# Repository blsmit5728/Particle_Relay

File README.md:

# Particle_Relay

Inspiration Relay board: https://www.sparkfun.com/products/15093

Main Controller to be used: https://docs.particle.io/datasheets/wi-fi/photon-datasheet/

Parts Repository: https://github.com/sparkfun/SparkFun-Eagle-Libraries

Power Input Requested: USB MicroB or MiniB at 5VDC

Use Case:
- Control a Garage door opener and monitor a GPIO for Opeen/Closed Status
- D7 controls Relay state
- D0 Ouptut to sense switch 3.3VDC
- D1 Input to Read the status of the reed switch.

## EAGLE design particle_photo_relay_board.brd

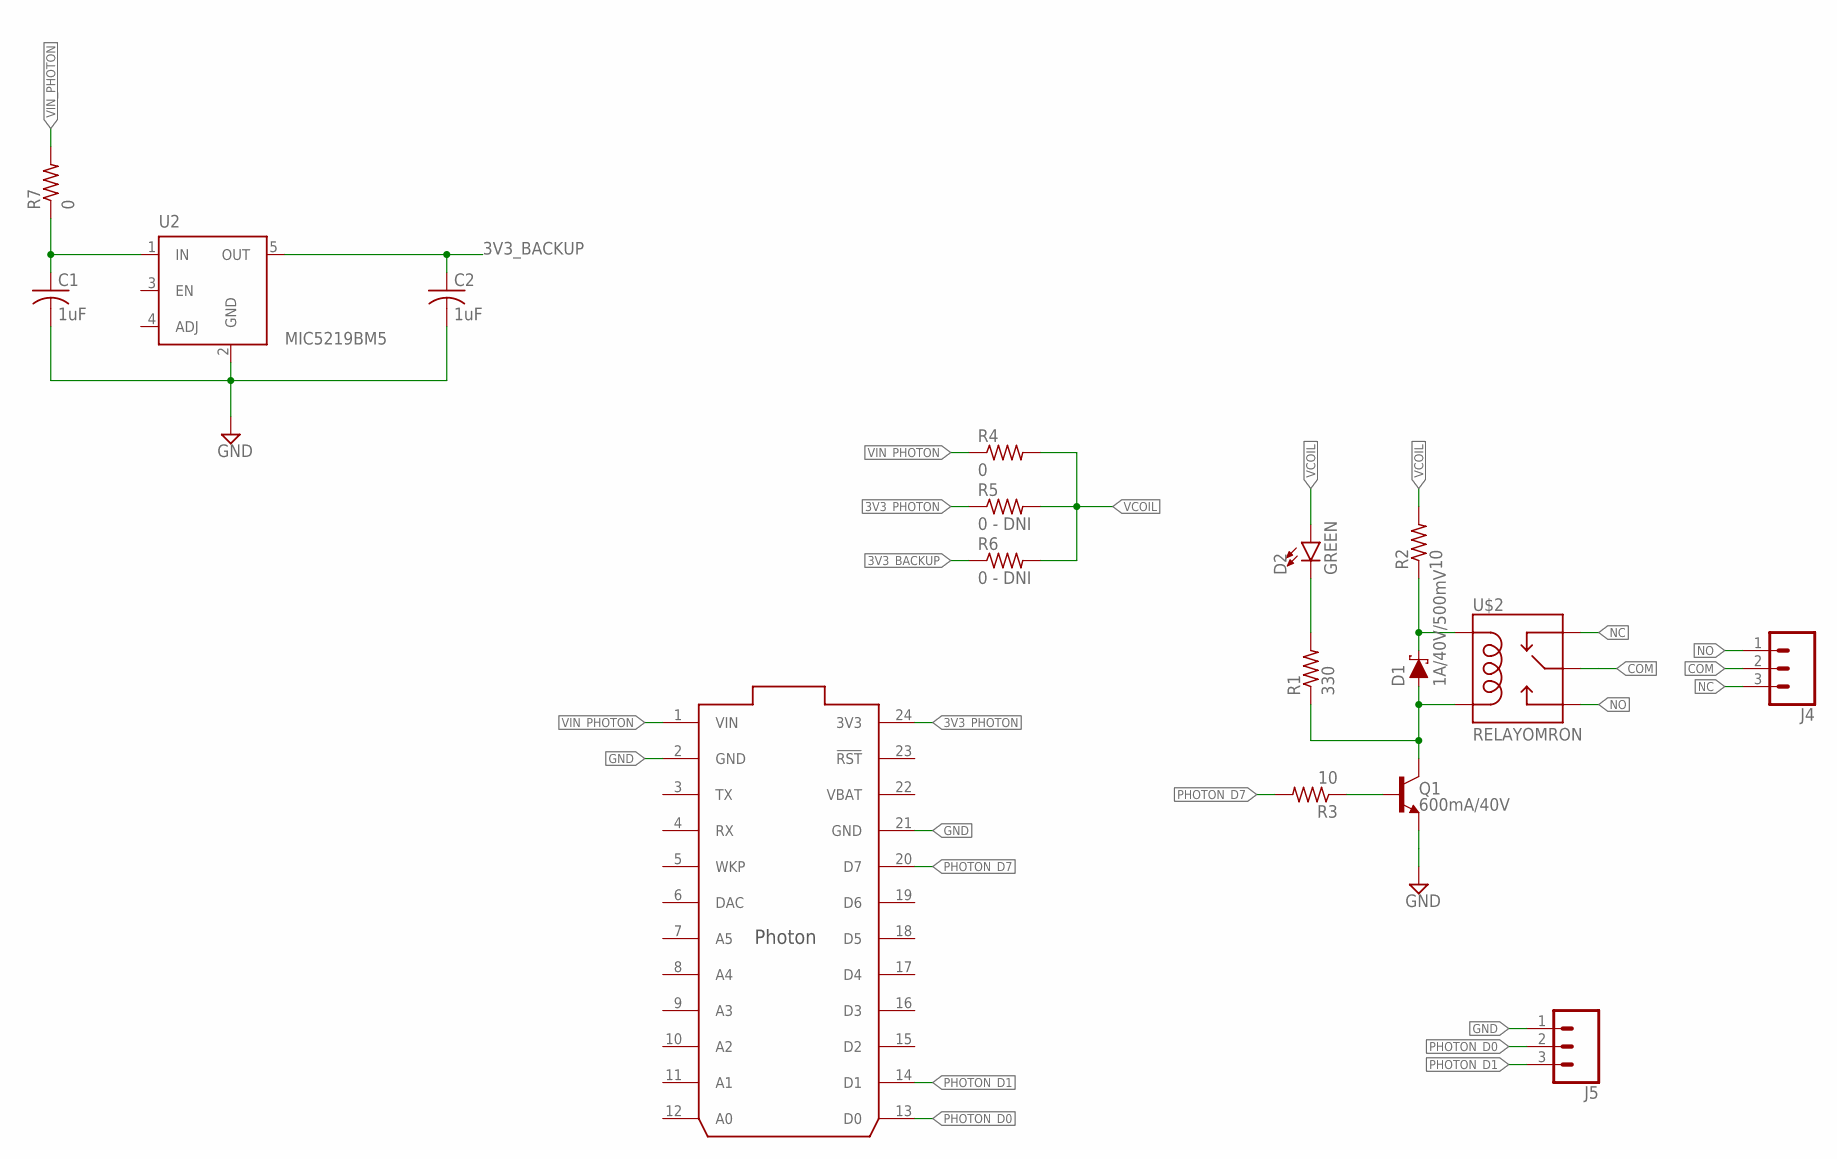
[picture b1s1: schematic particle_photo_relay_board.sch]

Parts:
C1, C2: 1uF; C0805
D1: 1A/40V/500mV; SMA-DIODE
D2: GREEN; LED-1206
J4, J5: CONN_03-SCREW-5MM; SCREWTERMINAL-5MM-3
Q1: 600mA/40V; SOT23-3
R1: 330; R0805
R2, R3: 10; R0805
R4, R7: 0; R0805
R5, R6: 0 - DNI; R0805
U2: MIC5219BM5; SOT23-5
U$1: PHOTON_WITH_HEADERS; PHOTON
U$2: RELAYOMRON; G5LE-14-DC5

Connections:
3V3_BACKUP: C2.1, R6.1, U2.5 (OUT)
3V3_PHOTON: R5.1, U$1.24 (3V3)
COM: J4.2, U$2.COMMON (MAIN)
GND: C1.2, C2.2, J5.1, Q1.2 (E), U2.2 (GND), U$1.2 (GND), U$1.21 (GND)
unnamed: D1.A, Q1.3 (C), R1.1, U$2.COIL2
unnamed: D1.C, R2.1, U$2.COIL1
unnamed: D2.C, R1.2
unnamed: Q1.1 (B), R3.1
NC: J4.3, U$2.CLOSED (NC)
NO: J4.1, U$2.OPEN (NO)
PHOTON_D0: J5.2, U$1.13 (D0)
PHOTON_D1: J5.3, U$1.14 (D1)
PHOTON_D7: R3.2, U$1.20 (D7)
VBAT: U$1.22 (VBAT)
VBUS_BACKUP: C1.1, R7.1, U2.1 (IN)
VCOIL: D2.A, R2.2, R4.2, R5.2, R6.2
VIN_PHOTON: R4.1, R7.2, U$1.1 (VIN)

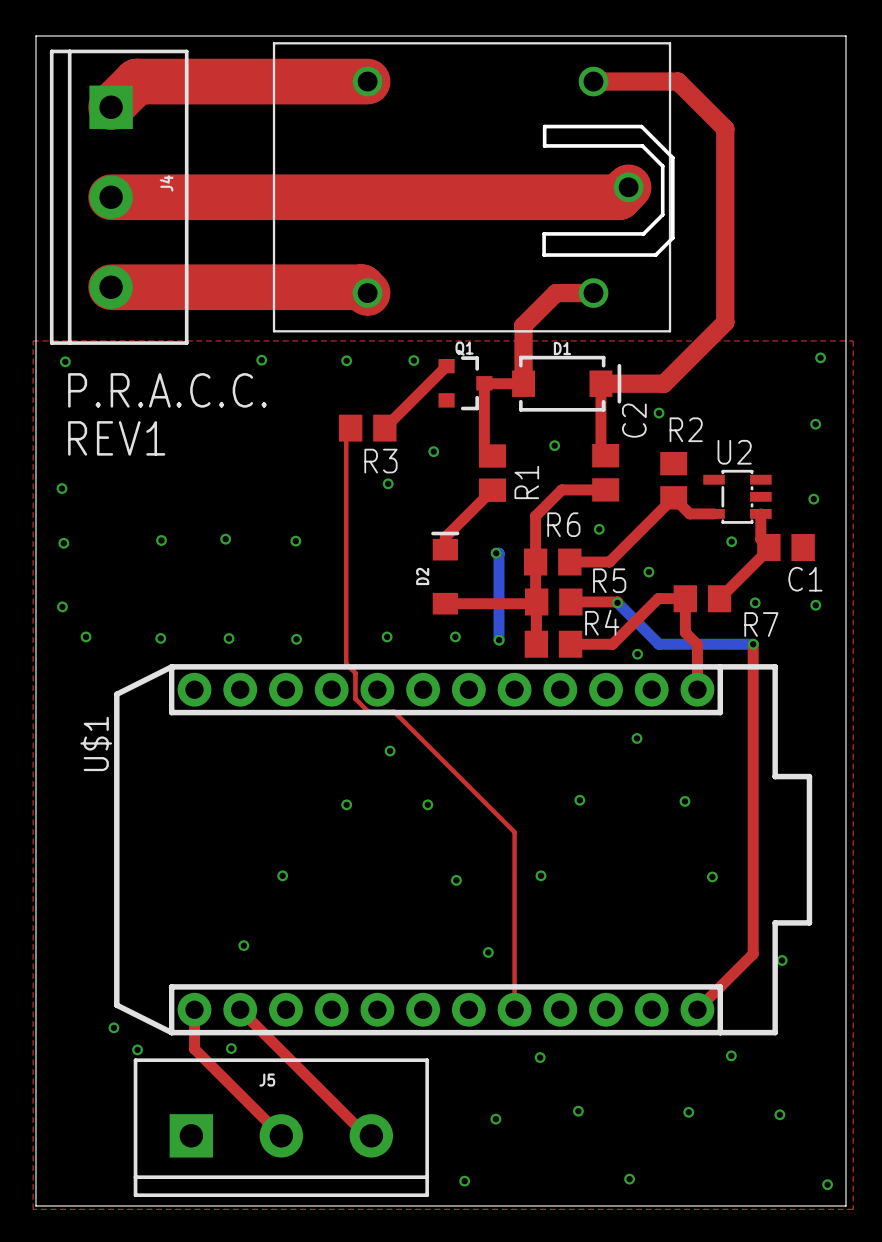
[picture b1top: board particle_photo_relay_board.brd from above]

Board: 2 copper layers, 44.8 x 64.8 mm, 17 parts (0 on the bottom side), 16 nets.

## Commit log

2019-01-16 Adding the board files for collaboration
2019-01-17 Laid out a pelim draft of the board
2019-01-27 Add files via upload
    P.R.A.C.C REV1 SCH and BRD files ready for review.
2019-01-28 Create PRACC_BOM.txt
    Adding P.R.A.C.C. BOM
    Total Parts Cost ~$36

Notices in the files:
parts and their libraries:
SparkFun-DiscreteSemi: Licensing: Creative Commons ShareAlike 4.0 International - https://creativecommons.org/licenses/by-sa/4.0
Particle-Devices: Licensing: Designed by Particle.
